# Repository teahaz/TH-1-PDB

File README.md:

# TH-1/PDB

An NRF52840 development board which fits into a framework compatible expansion slot. Designed to be a prototype for the TH-1 coprocessor.

> Teahaz 1: Prototype Development Board

---

# Version 1

> PDB adapted to fit inside a Framework compatible expansion card.
> This version is not complete or tested yet.

# Version 0

>  A quick and dirty implementation to check wether the NRF module works and is manufacturable (by me at home)

> (it worked)

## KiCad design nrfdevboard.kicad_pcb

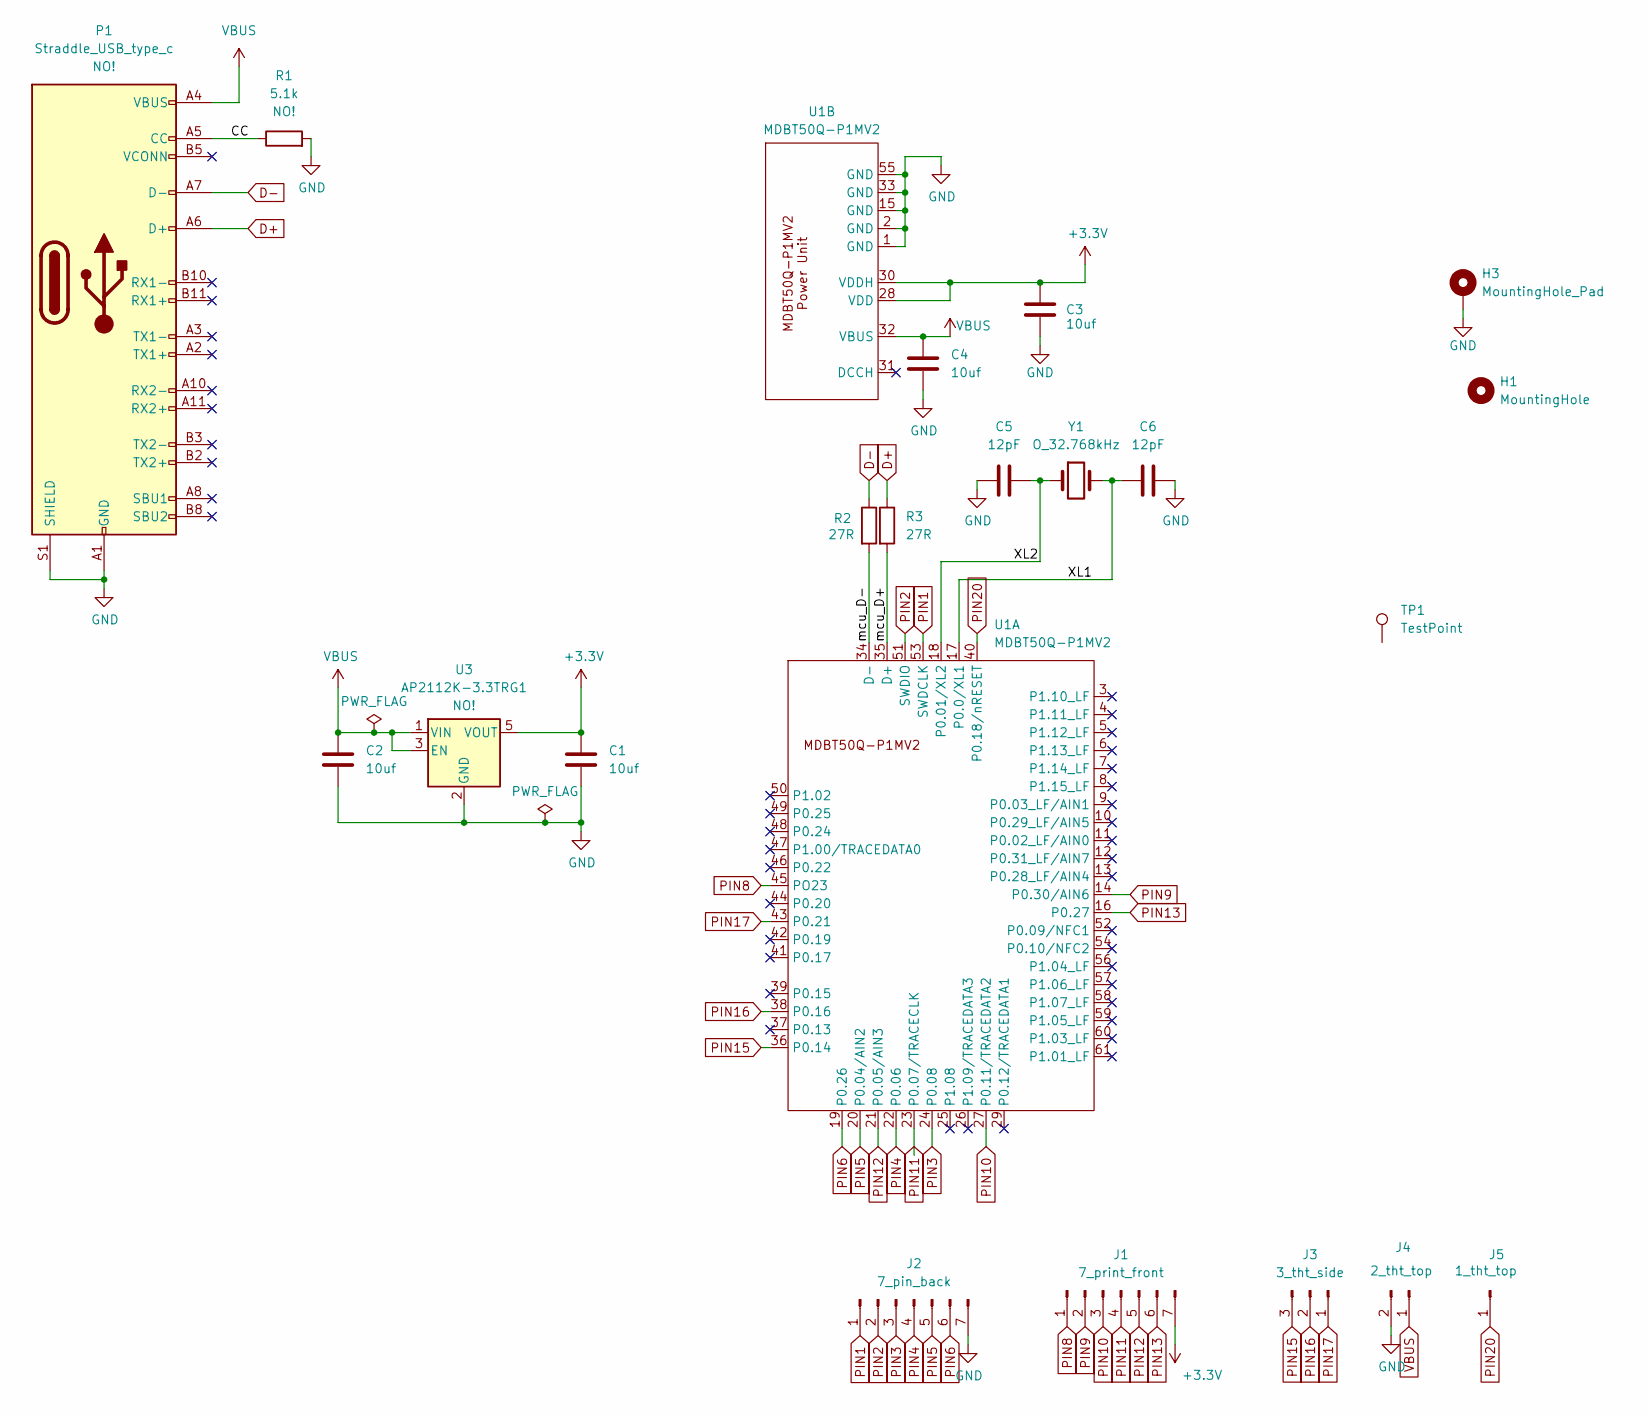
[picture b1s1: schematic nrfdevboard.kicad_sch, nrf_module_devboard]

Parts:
C1, C2, C3, C4: 10uf; C_0805_2012Metric; Mfr. Part no. CL21B106KOQNNNE; LCSC Part no. C95841
C5, C6: 12pF; C_0603_1608Metric; Mfr. Part no. CL10C120JB8NNNC; LCSC Part no. C38523
H1: MountingHole; PDB_MountingHole_left_2.2mm_M2
H3: MountingHole_Pad; PDB_MountingHole_right_2.2mm_M2_Pad
J1: 7_print_front; 7_side_pin
J2: 7_pin_back; 7_side_pin
J3: 3_tht_side; PinHeader_1x03_P2.54mm_Vertical
J4: 2_tht_top; PinHeader_1x02_P2.54mm_Vertical
J5: 1_tht_top; PinHeader_1x01_P2.54mm_Vertical
P1: Straddle_USB_type_c; USBC; Mfr. Part no. TYPE-C 24P-GTJB 040; LCSC Part no. C3151751
R1: 5.1k; R_0603_1608Metric; Mfr. Part No. RT0603BRD075K1L; LCSC Part no. C122969
R2, R3: 27R; R_0603_1608Metric; Mfr. Part No. 0603WAF270JT5E; LCSC Part no. C25190
TP1: TestPoint
U1: MDBT50Q-P1MV2; TH_MDBT50Q-P1MV2; Mfr Part no. MDBT50Q-P1MV2; LCSC Part no. C5119772
U3: AP2112K-3.3TRG1; SOT-23-5; Mfr. Part no. AP2112K-3.3TRG1; LCSC Part no. C23380830
Y1: O_32.768kHz; Crystal_SMD_3215-2Pin_3.2x1.5mm; Mfr. Part no. Q13FC13500003; LCSC Part no. C99010

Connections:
+3.3V: C1.1, C3.1, J1.7, U1.28 (VDD), U1.30 (VDDH), U3.5 (VOUT)
/CC: P1.A5 (CC), R1.1
/XL1: C6.1, U1.17 (P0.0/XL1), Y1.2
/XL2: C5.2, U1.18 (P0.01/XL2), Y1.1
/mcu_D+: R3.2, U1.35 (D+)
/mcu_D-: R2.2, U1.34 (D-)
D+: P1.A6 (D+), R3.1
D-: P1.A7 (D-), R2.1
GND: C1.2, C2.2, C3.2, C4.2, C5.1, C6.2, H3.1, J2.7, J4.2, P1.A1 (GND), P1.A12 (GND), P1.B1 (GND), P1.B12 (GND), P1.S1 (SHIELD), R1.2, U1.1 (GND), U1.2 (GND), U1.15 (GND), U1.33 (GND), U1.55 (GND), U3.2 (GND)
PIN1: J2.1, U1.53 (SWDCLK)
PIN2: J2.2, U1.51 (SWDIO)
PIN3: J2.3, U1.24 (P0.08)
PIN4: J2.4, U1.22 (P0.06)
PIN5: J2.5, U1.20 (P0.04/AIN2)
PIN6: J2.6, U1.19 (P0.26)
PIN8: J1.1, U1.45 (PO23)
PIN9: J1.2, U1.14 (P0.30/AIN6)
PIN10: J1.3, U1.27 (P0.11/TRACEDATA2)
PIN11: J1.4, U1.23 (P0.07/TRACECLK)
PIN12: J1.5, U1.21 (P0.05/AIN3)
PIN13: J1.6, U1.16 (P0.27)
PIN15: J3.3, U1.36 (P0.14)
PIN16: J3.2, U1.38 (P0.16)
PIN17: J3.1, U1.43 (P0.21)
PIN20: J5.1, U1.40 (P0.18/nRESET)
VBUS: C2.1, C4.1, J4.1, P1.A4 (VBUS), P1.A9 (VBUS), P1.B4 (VBUS), P1.B9 (VBUS), U1.32 (VBUS), U3.1 (VIN), U3.3 (EN)

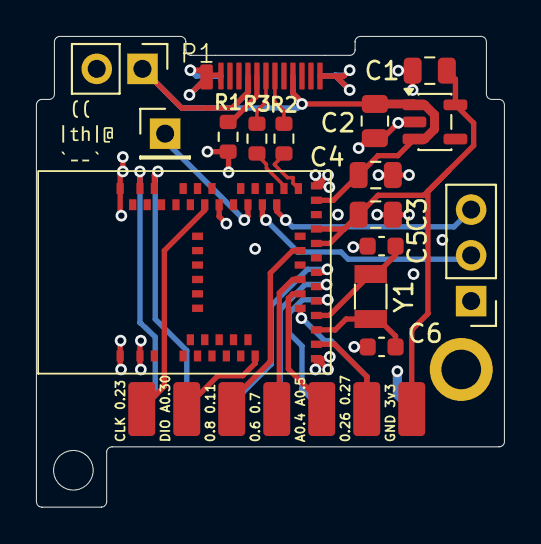
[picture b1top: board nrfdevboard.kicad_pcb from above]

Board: 4 copper layers, 26.0 x 26.2 mm, 20 parts (1 on the bottom side), 26 nets.

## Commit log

2026-03-27 Schematic
2026-03-28 Finished p1
2026-03-28 Teardrops and grid origins.
2026-04-19 PDBv2: Redesign for a framework module
    V2 brings two main changes. Firstly the size has been greatly reduced to
    fit into a framework module. With only 7 pins now.
    Additionally, v1 had issues when running from 5v USB. I am still not
    sure what this issue is since its identical to the datasheet, but I'm
    now including an external voltage regulator to run the chip at 3v3. This
    also reduces the BOM.
2026-04-19 Minor tweaks
2026-04-19 Add fw expansion case and proper usbc footprint
2026-04-20 Initial routing + 7 more GPIO pins
2026-04-21 Routing done (outside USB) + added some more pins
2026-04-22 Basics done. Will need to optimise double check DFM before manufacturing
2026-05-04 Clearing up DRC errors (part 1)
2026-05-05 Fixed remaining DRC errors
